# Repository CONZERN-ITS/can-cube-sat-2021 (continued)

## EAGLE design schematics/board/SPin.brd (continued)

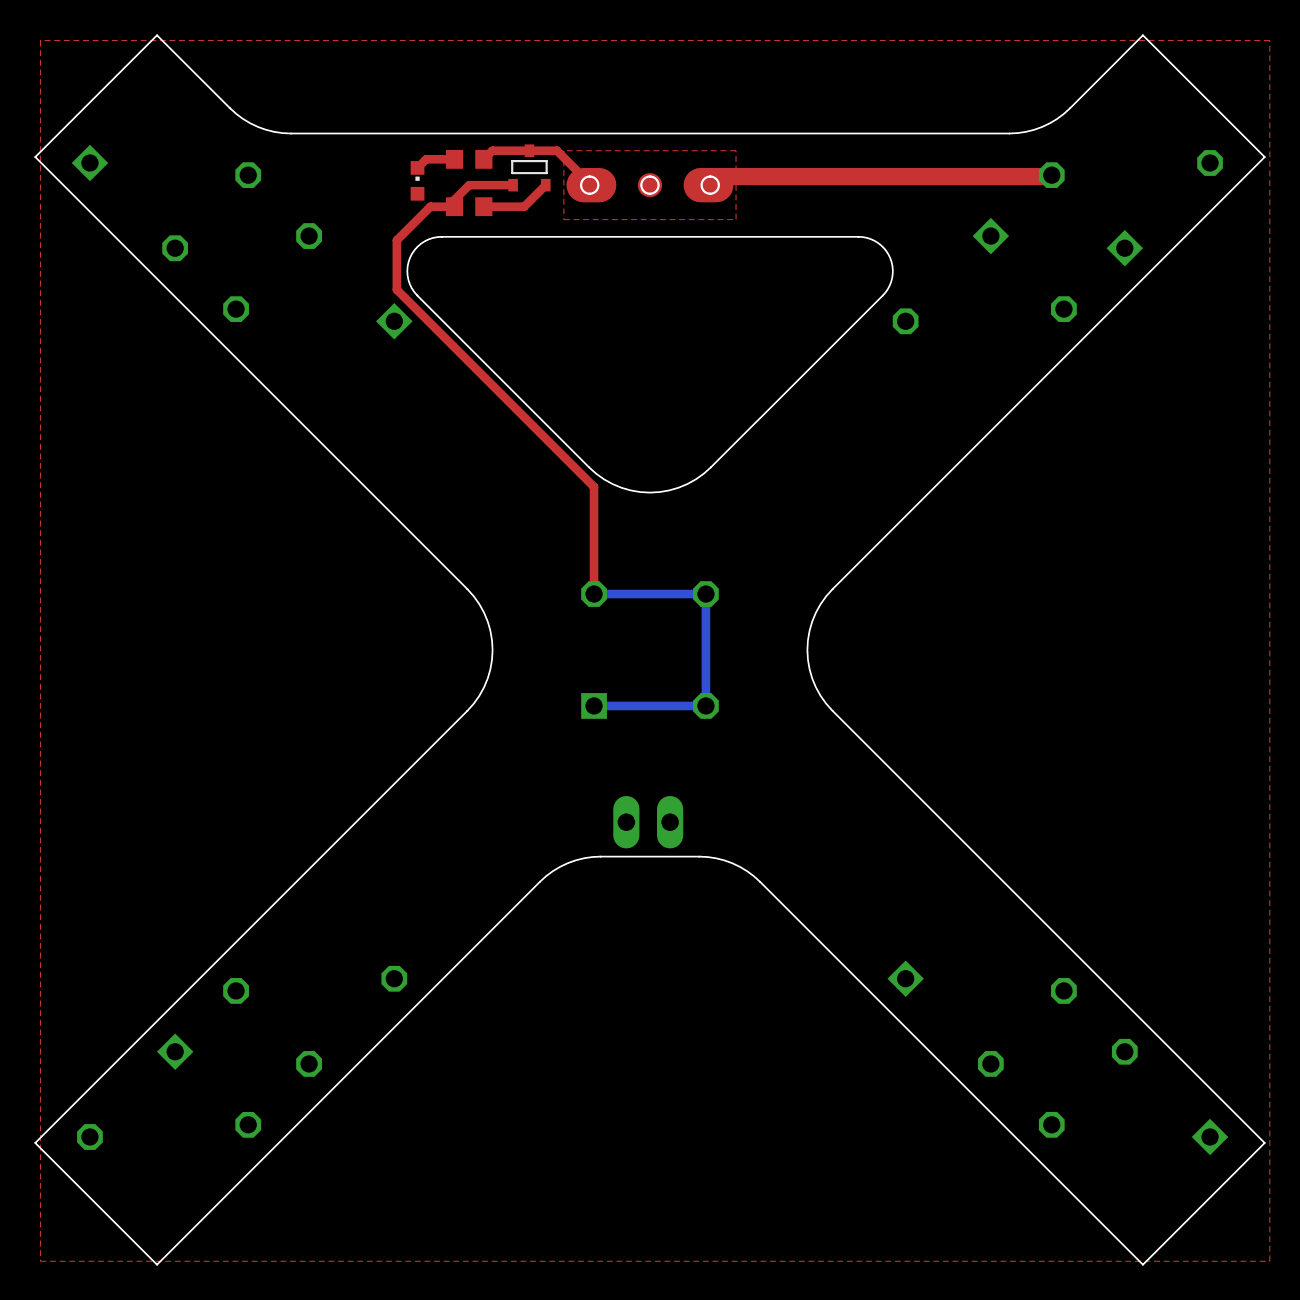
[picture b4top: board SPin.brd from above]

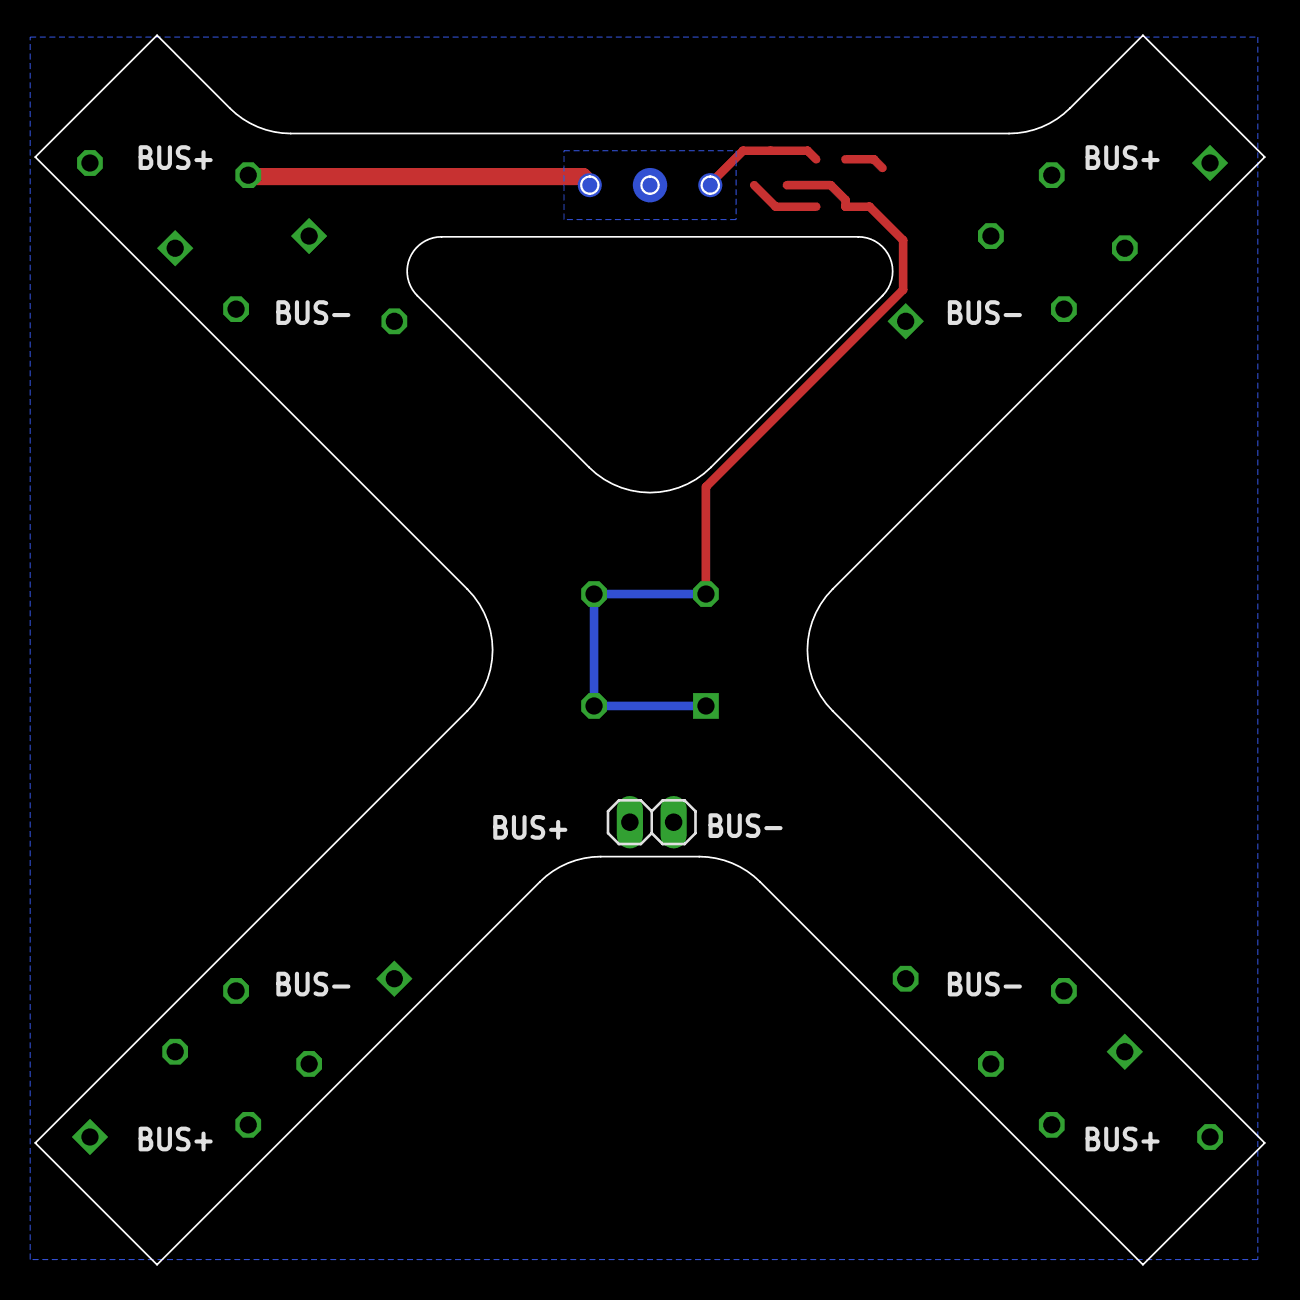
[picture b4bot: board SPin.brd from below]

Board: 2 copper layers, 71.4 x 71.4 mm, 15 parts (9 on the bottom side), 6 nets.

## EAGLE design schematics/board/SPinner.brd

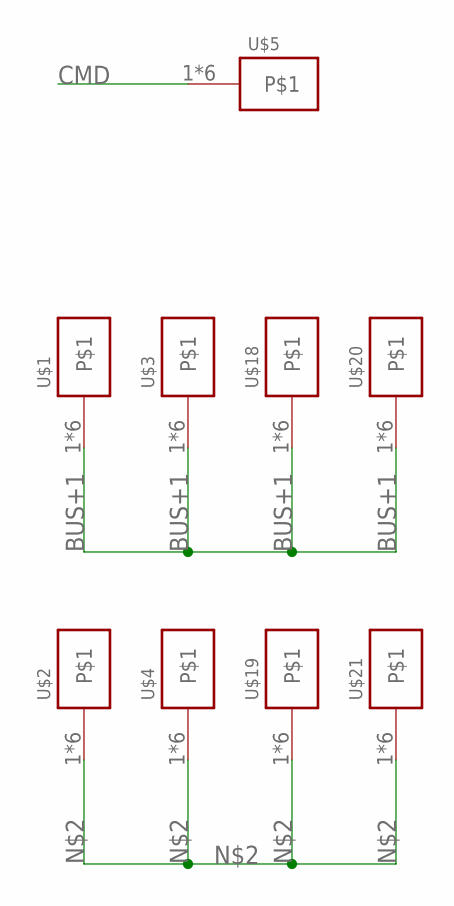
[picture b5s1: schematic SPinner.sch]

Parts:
U$1, U$2, U$3, U$4, U$18, U$19, U$20, U$21: KCONNECT
U$5: KCONNECTQUAD; KCONNECT_QUAD

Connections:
BUS+1: U$1.1, U$1.2, U$1.3, U$1.4, U$1.P$1, U$1.P$2, U$3.1, U$3.2, U$3.3, U$3.4, U$3.P$1, U$3.P$2, U$18.1, U$18.2, U$18.3, U$18.4, U$18.P$1, U$18.P$2, U$20.1, U$20.2, U$20.3, U$20.4, U$20.P$1, U$20.P$2
CMD: U$5.1, U$5.2, U$5.3, U$5.4, U$5.P$1, U$5.P$2
unnamed: U$2.1, U$2.2, U$2.3, U$2.4, U$2.P$1, U$2.P$2, U$4.1, U$4.2, U$4.3, U$4.4, U$4.P$1, U$4.P$2, U$19.1, U$19.2, U$19.3, U$19.4, U$19.P$1, U$19.P$2, U$21.1, U$21.2, U$21.3, U$21.4, U$21.P$1, U$21.P$2

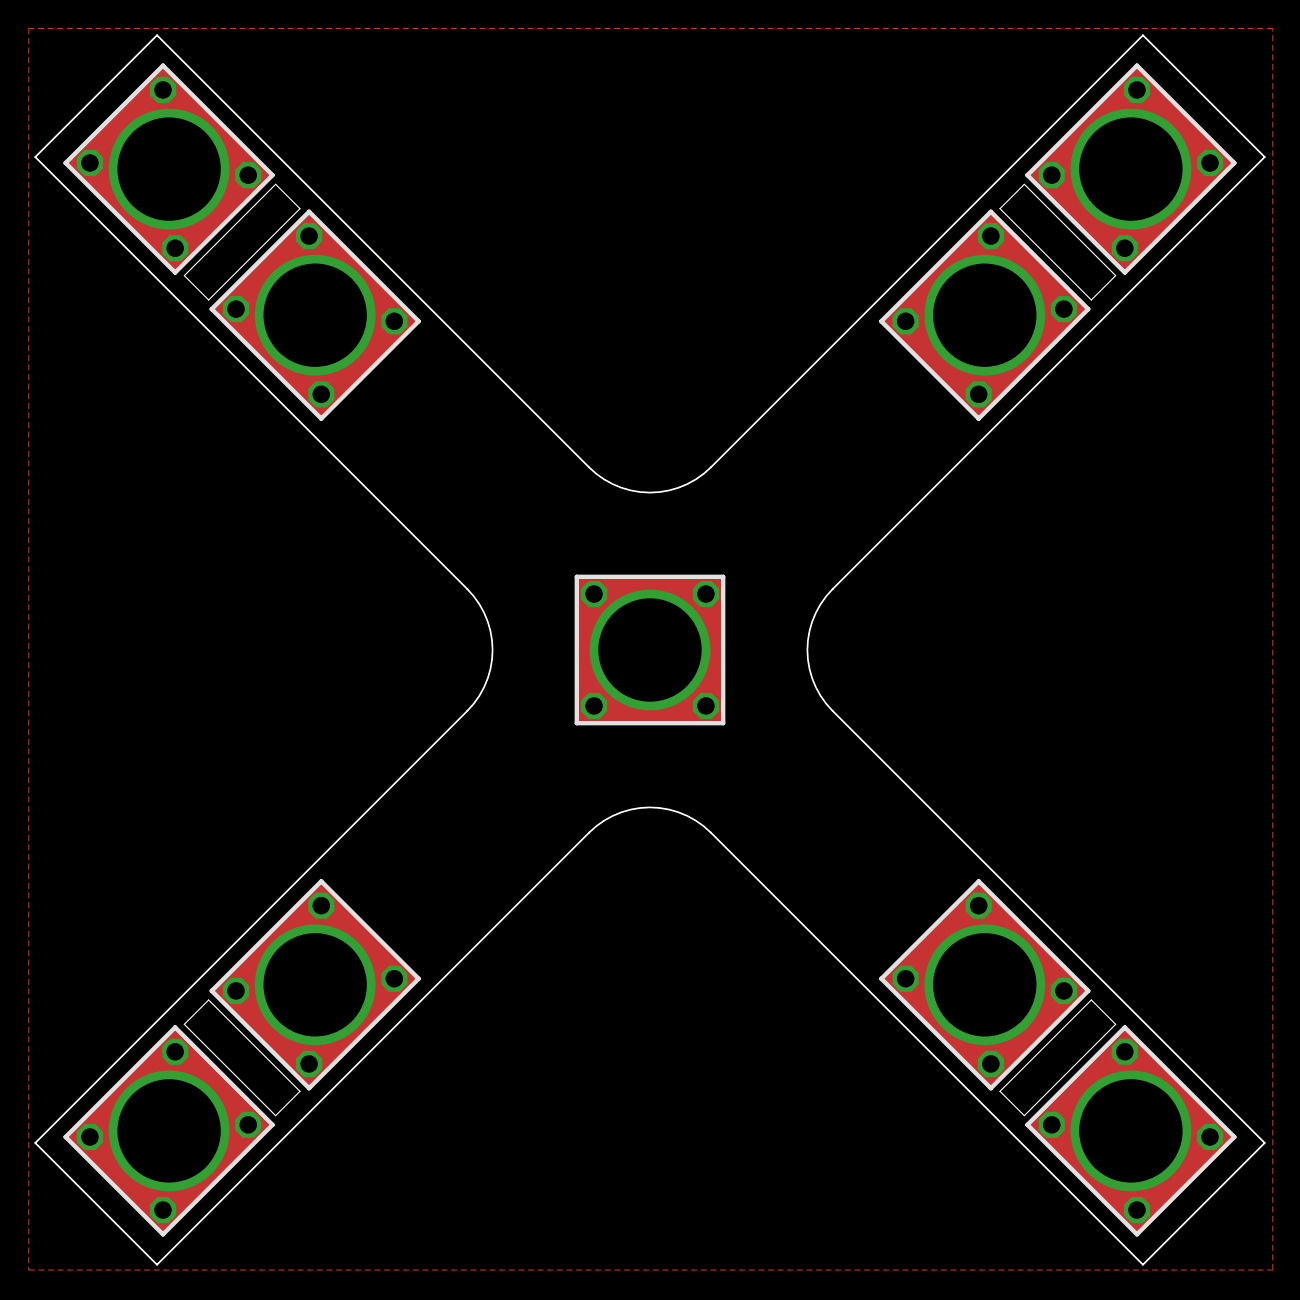
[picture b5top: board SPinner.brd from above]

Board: 2 copper layers, 71.4 x 71.4 mm, 9 parts (0 on the bottom side), 3 nets.

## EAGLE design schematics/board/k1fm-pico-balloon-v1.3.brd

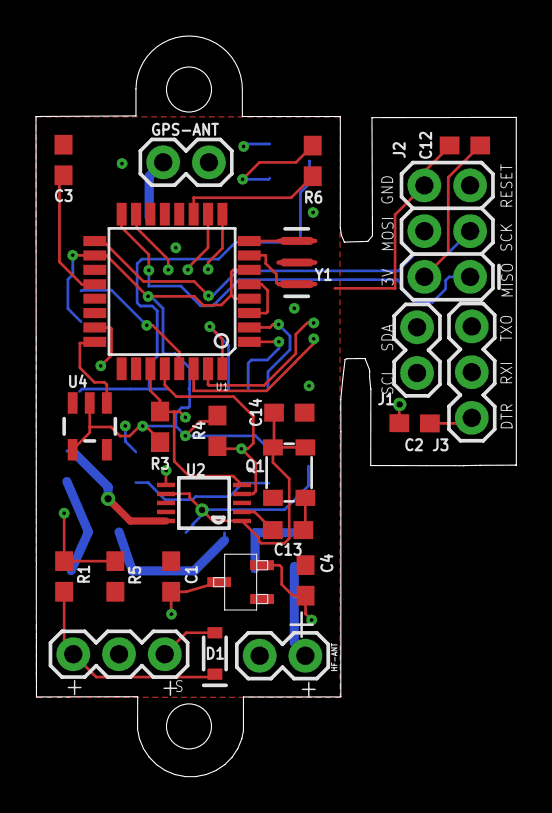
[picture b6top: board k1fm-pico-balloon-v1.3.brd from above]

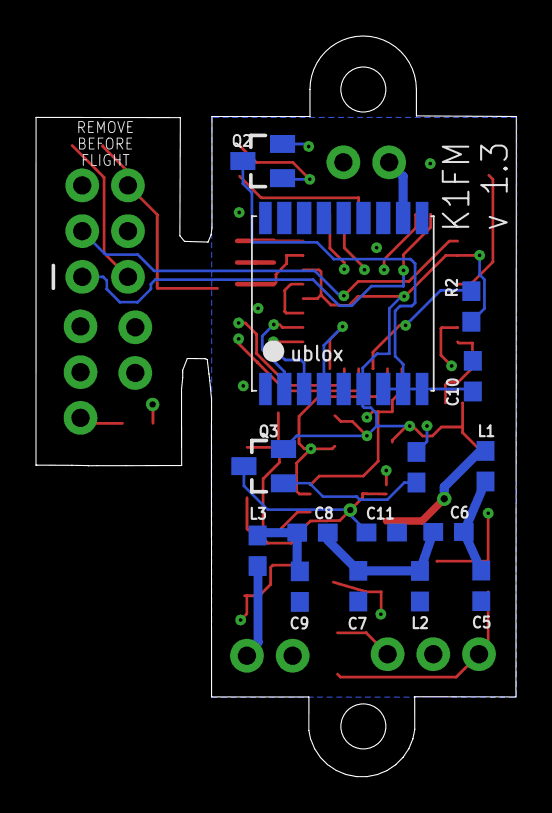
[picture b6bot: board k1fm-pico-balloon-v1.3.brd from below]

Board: 4 copper layers, 26.7 x 41.1 mm, 40 parts (15 on the bottom side), 36 nets.

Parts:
C1, C4, C12: 1.0uF; 0603
C2, C3: 0.1uF; 0603
C5, C9: 56pF; 0603
C6, C8: 18pF; 0603
C7: 47pF; 0603
C10, C11: 0.47uF; 0603
C13: 10nF; 0603
C14: 100nF; 0603
D1: 1A/23V/620mV; SOD-323
GPS1: UBLOX_MAX
GPS-ANT: GPS ANT; 1X02
HF-ANT: HF ANT; 1X02
J1: I2C; 1X02
J2: ICSP; 2X3
J3: SERIAL; 1X03
J4: POWER; 1X03
L1, L2, L3: 1.5uH; 0603
Q1: ASTX-H11-25.000MHZ-T; 3.2X2.5_KXO-84
Q2, Q3: DMP2305U; SOT23
R1, R3, R4: 4.7k; 0603
R2: 10k; 0603
R5: 1k; 0603
R6, R8: 1K; 0603
U1: ATMEGA328; TQFP32-08
U2: Si5351A-B-GT; MSOP10
U3: MCP1754X-XXXXX/C; SOT-23A_MC
U4: TMP36; SOT-23
Y1: 8/16/20MHz; RESONATOR-SMD-1:1

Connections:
3V: C4.1, C12.1, GPS1.6_V_BCKP, J2.2, Q2.2, Q3.2, R2.2, R3.2, R4.1, U1.4, U1.6, U1.18, U3.2, U4.2, U4.4
ANT: HF-ANT.1, L3.2
AREF: C3.2, U1.20
CLK0: L1.1, U2.10
CLK2: U1.9, U2.6
DTR: C2.1, J3.1
GND: C1.2, C3.1, C4.2, C5.1, C7.1, C9.1, C10.2, C11.2, C12.2, C14.1, GPS1.1_GND, GPS1.10_GND, GPS1.12_GND, GPS1.15_RESERVED, GPS-ANT.1, HF-ANT.2, J2.6, J4.2, L2.2, Q1.2, R5.1, U1.3, U1.5, U1.21, U2.8, U3.1, U4.5, Y1.2
GPS_E: R6.1, U1.11
MISO: J2.1, U1.16
MOSI: J2.4, U1.15
unnamed: C13.1, Q1.3
unnamed: C13.2, U2.2
unnamed: D1.A, J4.3
unnamed: Q2.1, R6.2
unnamed: GPS1.11_RF_IN, GPS-ANT.2
unnamed: Q3.1, R8.2
unnamed: C10.1, GPS1.7_VCC_IO, GPS1.8_VCC, GPS1.9_V_RESET, Q2.3
unnamed: C6.1, C7.2, C8.2, L2.1
unnamed: C5.2, C6.2, L1.2
unnamed: C8.1, C9.2, L3.1
unnamed: C11.1, C14.2, Q1.1, Q1.4, Q3.3, U2.1, U2.7
unnamed: U1.8, Y1.3
unnamed: U1.7, Y1.1
RESET: C2.2, J2.5, R2.1, U1.29
RXD: J3.3, U1.30
RXI: GPS1.2_TXD1, U1.2
SCK: J2.3, U1.17
SCL: J1.2, R4.2, U1.28, U2.4
SDA: J1.1, R3.1, U1.27, U2.5
TEMP: U1.24, U4.1
TIMEP: GPS1.4_TIMEPULSE, U1.32
TXD: J3.2, U1.31
TXO: GPS1.3_RXD1, U1.1
TX_E: R8.1, U1.10
VDD: C1.1, D1.C, J4.1, R1.1, U3.3
VDD_TST: R1.2, R5.2, U1.23
